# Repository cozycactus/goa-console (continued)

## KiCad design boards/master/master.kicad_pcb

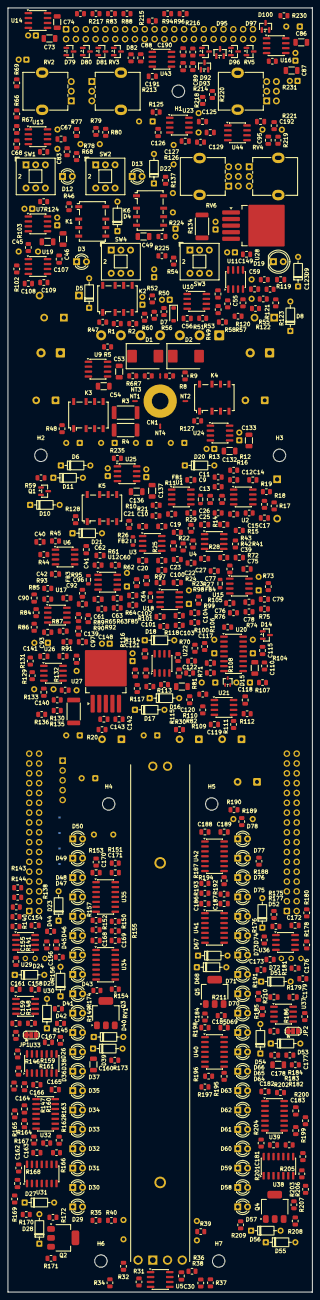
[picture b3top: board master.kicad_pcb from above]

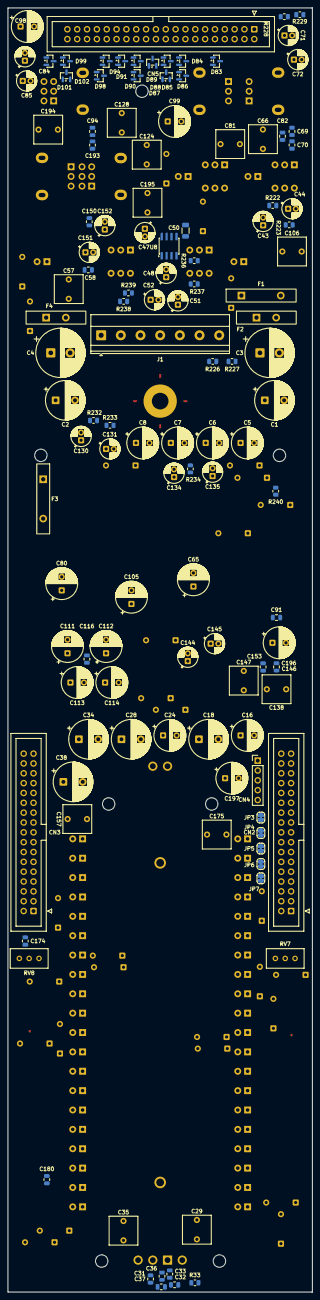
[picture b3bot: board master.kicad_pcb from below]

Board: 4 copper layers, 78.6 x 331.5 mm, 639 parts (122 on the bottom side), 387 nets, no tracks yet.

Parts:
C1, C2: 470u 25V; CP_Radial_D10.0mm_P5.00mm
C3, C4: 1000u 25V; CP_Radial_D12.5mm_P5.00mm
C5, C6, C7, C8: 47u 25V; CP_Radial_D8.0mm_P3.50mm
C9, C10, C14, C15, C19, C20, C26, C27, C30, C31, C41, C42, C55, C56, C58, C59, C60, C61, C67, C68, C75, C76, C92, C93, C100, C101, C107, C108, C115, C116, C117, C118, C119, C121, C122, C125, C126, C139, C140, C142, C143, C149, C150, C154, C155, C158, C159, C162, C163, C164, C165, C166, C167, C168, C169, C170, C171, C172, C173, C176, C177, C180, C181, C182, C183, C184, C185, C186, C187, C188, C189, C190, C191, C192, C193: 100n; C_0805_2012Metric
C11, C17, C21, C25, C33, C37, C39, C62, C69, C77, C82, C88, C89, C94, C95, C102, C146, C153: 100p C0G; C_0805_2012Metric
C12, C13, C22, C23, C63, C64, C78, C79, C103, C104: 22p C0G 5%; C_0805_2012Metric
C16, C24, C65, C80, C98, C99, C105, C111, C112, C113, C114, C196, C197: 33u NP 25V; CP_Radial_D8.0mm_P3.50mm
C18, C28, C34, C38: 100u NP 25V; CP_Radial_D10.0mm_P5.00mm
C29, C35, C66, C81, C106, C124, C128, C138, C147, C157, C175, C194, C195: 2.2u film; C_Rect_L7.2mm_W7.2mm_P5.00mm_FKS2_FKP2_MKS2_MKP2
C32, C36, C70, C83: 10p C0G; C_0805_2012Metric
C40, C109, C127, C129, C141, C148, C156, C161, C174, C179: 22p C0G; C_0805_2012Metric
C43, C44, C47, C48, C51, C52, C71, C72, C84, C85, C130, C131, C134, C135, C144, C145, C151, C152: 10u NP 25V; CP_Radial_D5.0mm_P2.00mm
C45, C46, C49, C50, C53, C54, C73, C74, C86, C87, C110, C120, C132, C133, C136, C137, C160, C178: 1u; C_1206_3216Metric
C57: 2.2u film 63V; C_Rect_L7.2mm_W7.2mm_P5.00mm_FKS2_FKP2_MKS2_MKP2
C90, C91, C96, C97: 33p C0G; C_0805_2012Metric
C123: 330n; C_0805_2012Metric
CN1: Ground bar M4 (star point); MountingHole_4.3mm_M4_Pad
CN2: Bus L wing 2x17; IDC-Header_2x17_P2.54mm_Vertical
CN3: Bus R wing 2x17; IDC-Header_2x17_P2.54mm_Vertical
CN4: Remote meter; PinHeader_1x05_P2.54mm_Vertical
CN5: Jack board link 2x20; IDC-Header_2x20_P2.54mm_Vertical
D1, D2: SS54; D_SMC
D3: Power green; LED_D3.0mm
D4, D5, D6, D8, D9, D10, D11, D16, D17, D18, D20, D21, D22, D23, D24, D25, D26, D27, D28, D39, D40, D51, D52, D53, D54, D55, D56, D67, D68: 1N4148; D_DO-35_SOD27_P7.62mm_Horizontal
D7: BZT52C6V2; D_SOD-123
D12: Aux 5 AFL red; LED_D3.0mm
D13: Aux 6 AFL red; LED_D3.0mm
D14: BZX84C5V1; SOT-23
D15: BAT54W; SOT-323_SC-70
D19: PFL ACTIVE red 5mm; LED_D5.0mm
D29, D57: green -20 dB; LED_D3.0mm
D30, D58: green -18 dB; LED_D3.0mm
D31, D59: green -16 dB; LED_D3.0mm
D32, D60: green -14 dB; LED_D3.0mm
D33, D61: green -12 dB; LED_D3.0mm
D34, D62: green -10 dB; LED_D3.0mm
D35, D63: green -8 dB; LED_D3.0mm
D36, D64: green -6 dB; LED_D3.0mm
D37, D65: green -4 dB; LED_D3.0mm
D38, D66: green -2 dB; LED_D3.0mm
D41, D69: green +0 dB; LED_D3.0mm
D42, D70: amber +2 dB; LED_D3.0mm
D43, D71: amber +4 dB; LED_D3.0mm
D44, D72: amber +6 dB; LED_D3.0mm
D45, D73: amber +8 dB; LED_D3.0mm
D46, D74: amber +10 dB; LED_D3.0mm
D47, D75: red +12 dB; LED_D3.0mm
D48, D76: red +14 dB; LED_D3.0mm
D49, D77: red +16 dB; LED_D3.0mm
D50, D78: red +18 dB; LED_D3.0mm
D79, D80, D81, D82, D83, D84, D85, D86, D87, D88, D89, D90, D91, D92, D93, D94, D95, D96, D97, D98, D99, D100, D101, D102: BAV199; SOT-23
F1, F3: MF-RX250/72; Fuse_Bourns_MF-RX250-72_Radial_P10.16mm
F2, F4: MF-RX185/72; Fuse_Bourns_MF-RX185-72_Radial_P5.08mm
FB1, FB2, FB3, FB4, FB5: Ferrite 220R@100MHz; L_0805_2012Metric
H1, H2, H3, H4, H5, H6, H7: M3 standoff 11.5 mm; MountingHole_3.2mm_M3
J1: PSU in (NC7MD-LX); TerminalBlock_Phoenix_MKDS-1,5-7-5.08_1x07_P5.08mm_Horizont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
JP1, JP2: PEAK(1-2) / AVG; SolderJumper-3_P1.3mm_Bridged12_RoundedPad1.0x1.5mm
JP3: SPARE1 to GNDA; SolderJumper-2_P1.3mm_Bridged_RoundedPad1.0x1.5mm
JP4: SPARE3 to GNDA; SolderJumper-2_P1.3mm_Bridged_RoundedPad1.0x1.5mm
JP5: SPARE5 to GNDA; SolderJumper-2_P1.3mm_Bridged_RoundedPad1.0x1.5mm
JP6: SPARE7 to GNDA; SolderJumper-2_P1.3mm_Bridged_RoundedPad1.0x1.5mm
JP7: SPARE19 to GNDA; SolderJumper-2_P1.3mm_Bridged_RoundedPad1.0x1.5mm
K1, K2, K3, K4, K5, K6: G6K-2F-Y DC12; Relay_DPDT_Omron_G6K-2F-Y
NT1: Star GNDA-GNDD; NetTie-2_SMD_Pad0.5mm
NT2: Star GNDA-GNDM; NetTie-2_SMD_Pad0.5mm
NT3: Star GNDA-PHONESGND; NetTie-2_SMD_Pad0.5mm
NT4: Star GNDA-CHASSIS; NetTie-2_SMD_Pad0.5mm
Q1: MMBT3904; SOT-23
Q2, Q3, Q4, Q5: BCP53-16; SOT-223
R1, R2: 1R; R_0805_2012Metric
R3, R4, R130, R134: 2R2; R_2512_6332Metric
R5, R6, R7, R8: 10R; R_0805_2012Metric
R9, R33, R38, R49, R56, R58, R59, R60, R67, R71, R78, R82, R104, R131, R135, R240: 4K7; R_0805_2012Metric
R10, R31, R36, R66, R70, R77, R81, R102, R109, R111, R116, R119, R120, R121, R125, R126, R129, R133: 100K; R_0805_2012Metric
R11, R21: 4K7 1%; R_0805_2012Metric
R12, R13, R14, R15, R22, R23, R24, R25, R62, R63, R64, R65, R73, R74, R75, R76, R98, R99, R100, R101: 2K2 0.1%; R_0805_2012Metric
R16, R19, R26, R29: 75R; R_0805_2012Metric
R17, R20, R27, R30, R35, R40, R51, R94, R96: 47K; R_0805_2012Metric
R18, R28: 1K; R_0805_2012Metric
R32, R37, R166, R203: 47R; R_0805_2012Metric
R34, R39, R132, R136: 2K2; R_0805_2012Metric
R41, R42, R43, R44, R45, R54, R113, R115, R118, R123, R139, R140, R142, R143, R148, R176, R177, R179, R180, R185, R239: 10K; R_0805_2012Metric
R46, R47, R48, R127, R128, R137: 560R; R_0805_2012Metric
R50: 56K; R_0805_2012Metric
R52, R69, R80: 22K; R_0805_2012Metric
R53: 64K9; R_0805_2012Metric
R55: 2M2; R_0805_2012Metric
R57: 22M; R_0805_2012Metric
R61, R72, R97: 22K 1%; R_0805_2012Metric
R68, R79: DNF (2K2 = +10 dB); R_0805_2012Metric
R83, R88, R105, R106, R107, R108, R122, R212, R217: 1M; R_0805_2012Metric
R84, R85, R86, R87, R89, R90, R91, R92: 10K 0.1%; R_0805_2012Metric
R93, R95, R103, R110, R112, R138, R175, R215, R216, R220, R221: 100R; R_0805_2012Metric
R114, R146, R183: 330K; R_0805_2012Metric
R117: 10M; R_0805_2012Metric
R124: 3K3; R_0805_2012Metric
R141, R178: 20K; R_0805_2012Metric
R144, R181: 33K; R_0805_2012Metric
R145, R159, R182, R196, R213, R214, R218, R219: 220R; R_0805_2012Metric
R147, R184: 220K; R_0805_2012Metric
R149, R156, R186, R193: 470R; R_0805_2012Metric
R150, R187: 16K; R_0805_2012Metric
R151, R188: 1K5; R_0805_2012Metric
R152, R189: 1K1; R_0805_2012Metric
R153, R190: 910R; R_0805_2012Metric
R154, R191: 680R; R_0805_2012Metric
R155, R192: 620R; R_0805_2012Metric
R157, R194: 330R; R_0805_2012Metric
R158, R195: 300R; R_0805_2012Metric
R160, R197: 180R; R_0805_2012Metric
R161, R198: 150R; R_0805_2012Metric
R162, R199: 110R; R_0805_2012Metric
R163, R170, R200, R207: 91R; R_0805_2012Metric
R164, R201: 68R; R_0805_2012Metric
R165, R202: 62R; R_0805_2012Metric
R167, R204: 33R; R_0805_2012Metric
R168, R205: 27R; R_0805_2012Metric
R169, R206: 20R; R_0805_2012Metric
R171, R173, R208, R210: 120R; R_0805_2012Metric
R172, R174, R209, R211: 27K; R_0805_2012Metric
R222, R223, R224, R225, R226, R227, R228, R229, R230, R231, R232, R233, R234, R235: 22R; R_0805_2012Metric
R236, R237: 91K; R_0805_2012Metric
R238: 51K; R_0805_2012Metric
RV1: Master fader 10K log 100mm dual; Potentiometer_Bourns_PTB0144_Slide_100mm_Dual
RV2: Aux 5 master 10K log; Potentiometer_Alpha_RD901F-40-00D_Single_Vertical
RV3: Aux 6 master 10K log; Potentiometer_Alpha_RD901F-40-00D_Single_Vertical
RV4: Solo level 10K log; Potentiometer_Alpha_RD901F-40-00D_Single_Vertical
RV5: C/Room level 10K log dual; Potentiometer_Alpha_RD902F-40-00D_Dual_Vertical
RV6: Phones level 10K log dual; Potentiometer_Alpha_RD902F-40-00D_Dual_Vertical
RV7, RV8: Cal 10K; Potentiometer_Bourns_3296W_Vertical
SW1: Aux 5 AFL; SW_Push_2P2T_Toggle_CK_PVA2xxH1xxxxxxV2
SW2: Aux 6 AFL; SW_Push_2P2T_Toggle_CK_PVA2xxH1xxxxxxV2
SW3: EXT select; SW_Push_2P2T_Toggle_CK_PVA2xxH1xxxxxxV2
SW4: C/Room DIM; SW_Push_2P2T_Toggle_CK_PVA2xxH1xxxxxxV2
U1, U2, U3, U4, U5, U6, U12, U13, U15, U17, U19, U23, U26: OPA1612; SOIC-8_3.9x4.9mm_P1.27mm
U7, U8, U9, U14, U16, U24, U25: DRV135; SOIC-8_3.9x4.9mm_P1.27mm
U10, U11, U22: LM393; SOIC-8_3.9x4.9mm_P1.27mm
U18, U21, U43, U44: OPA1656; SOIC-8_3.9x4.9mm_P1.27mm
U20: DG413; SOIC-16_3.9x9.9mm_P1.27mm
U27, U28: LME49600; TO-263-5_TabPin3
U29, U30, U36, U37: TL072; SOIC-8_3.9x4.9mm_P1.27mm
U31, U32, U33, U34, U35, U38, U39, U40, U41, U42: LM2901; SOIC-14_3.9x8.7mm_P1.27mm

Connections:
+5VL: C110.1, C115.1, D14.3, D15.1, R104.2, R116.1, U20.12
+VA: C1.1, C9.1, C14.1, C19.1, C26.1, C30.1, C41.1, C45.1, C49.1, C53.1, C60.1, C67.1, C73.1, C75.1, C86.1, C92.1, C100.1, C107.1, C116.1, C118.1, C125.1, C132.1, C136.1, C190.1, C192.1, D15.3, D79.2, D80.2, D81.2, D82.2, D83.2, D84.2, D85.2, D86.2, D87.2, D88.2, D89.2, D90.2, D91.2, D92.2, D93.2, D94.2, D95.2, D96.2, D97.2, D98.2, D99.2, D100.2, D101.2, D102.2, R1.2, R104.1, U1.8, U2.8, U3.8, U4.8, U5.8, U6.8, U7.6, U8.6, U9.6, U12.8, U13.8, U14.6, U15.8, U16.6, U17.8, U18.8, U19.8, U20.13, U21.8, U23.8, U24.6, U25.6, U43.8, U44.8
+VBUS: D1.1, F1.1, F3.1, J1.2, J1.3, R1.1, R3.1, R5.1, R7.1, R46.1, R47.1, R48.1, R49.1, R50.1, R127.1, R128.1, R137.1
+VBUS_L: CN2.32, CN2.33, CN2.34, F1.2
+VBUS_R: CN3.32, CN3.33, CN3.34, F3.2
+VL: C7.1, C55.1, C58.1, C121.1, R7.2, R9.1, R54.1, R58.1, R114.1, R119.1, R123.1, R124.1, SW1.5, SW2.5, U10.8, U11.8, U22.8
+VM: C5.1, C154.1, C158.1, C162.1, C164.1, C166.1, C168.1, C170.1, C172.1, C176.1, C180.1, C182.1, C184.1, C186.1, C188.1, CN4.3, D27.2, D39.2, D55.2, D67.2, R5.2, R150.1, R171.1, R173.1, R187.1, R208.1, R210.1, U29.8, U30.8, U31.3, U32.3, U33.3, U34.3, U35.3, U36.8, U37.8, U38.3, U39.3, U40.3, U41.3, U42.3
+VP: C3.1, C139.1, C142.1, C144.1, C149.1, C151.1, R3.2, U26.8, U27.5, U28.5
-VA: C2.2, C10.2, C15.2, C20.2, C27.2, C31.2, C42.2, C46.2, C50.2, C54.2, C61.2, C68.2, C74.2, C76.2, C87.2, C93.2, C101.2, C108.2, C117.2, C119.2, C126.2, C133.2, C137.2, C191.2, C193.2, D79.1, D80.1, D81.1, D82.1, D83.1, D84.1, D85.1, D86.1, D87.1, D88.1, D89.1, D90.1, D91.1, D92.1, D93.1, D94.1, D95.1, D96.1, D97.1, D98.1, D99.1, D100.1, D101.1, D102.1, R2.2, U1.4, U2.4, U3.4, U4.4, U5.4, U6.4, U7.5, U8.5, U9.5, U12.4, U13.4, U14.5, U15.4, U16.5, U17.4, U18.4, U19.4, U20.4, U21.4, U23.4, U24.5, U25.5, U43.4, U44.4
-VBUS: D2.2, F2.1, F4.1, J1.6, J1.7, R2.1, R4.1, R6.1, R8.1, R53.2
-VBUS_L: CN2.30, CN2.31, F2.2
-VBUS_R: CN3.30, CN3.31, F4.2
-VL: C8.2, C56.2, C59.2, C122.2, R8.2, U10.4, U11.4, U22.4
-VM: C6.2, C155.2, C159.2, C163.2, C165.2, C167.2, C169.2, C171.2, C173.2, C177.2, C181.2, C183.2, C185.2, C187.2, C189.2, CN4.5, D38.1, D50.1, D66.1, D78.1, R6.2, R172.2, R174.2, R209.2, R211.2, U29.4, U30.4, U31.12, U32.12, U33.12, U34.12, U35.12, U36.4, U37.4, U38.12, U39.12, U40.12, U41.12, U42.12
-VP: C4.2, C140.2, C143.2, C145.2, C150.2, C152.2, R4.2, U26.4, U27.3, U28.3
A5_AFLC: C194.2, R69.1
A5_AFLJ: R69.2, SW1.2
A5_MIX: C63.1, C65.1, R63.2, U12.7
A5_ON: C72.2, CN5.20, D90.3, U14.2
A5_OP: C71.2, CN5.19, D89.3, U14.7
A5_OUT: C69.1, C194.1, R67.1, U13.1, U14.4
A5_PT: C65.2, RV2.3
A5_SUM: C62.1, R61.1, R62.1, U12.1
A5_W: C66.1, RV2.2
A6_AFLC: C195.2, R80.1
A6_AFLJ: R80.2, SW2.2
A6_MIX: C78.1, C80.1, R74.2, U15.7
A6_ON: C85.2, CN5.23, D92.3, U16.2
A6_OP: C84.2, CN5.22, D91.3, U16.7
A6_OUT: C82.1, C195.1, R78.1, U13.7, U16.4
A6_PT: C80.2, RV3.3
A6_SUM: C77.1, R72.1, R73.1, U15.1
A6_W: C81.1, RV3.2
AUX1: CN2.24, CN3.24
AUX2: CN2.25, CN3.25
AUX3: CN2.23, CN3.23
AUX4: CN2.22, CN3.22
AUX5: CN2.21, CN3.21, FB3.1
AUX6: CN2.20, CN3.20, FB4.1
CHASSIS: CN5.9, J1.1, NT4.2
CRL_N: C131.2, K4.5, U24.2
CRL_P: C130.2, K4.4, U24.7
CRL_XN: CN5.32, D98.3, K4.6
CRL_XP: CN5.31, D97.3, K4.3
CRO_L: U23.1, U23.2, U24.4
CRO_R: U23.6, U23.7, U25.4
CRP_L: R236.2, RV5.3, SW4.3
CRP_R: R237.2, RV5.6, SW4.6
CRR_N: C135.2, K5.5, U25.2
CRR_P: C134.2, K5.4, U25.7
CRR_XN: CN5.35, D100.3, K5.6
CRR_XP: CN5.34, D99.3, K5.3
CRSB_L: R110.2, R138.1, R236.1, RV6.3, SW4.2
CRSB_LO: R110.1, U21.1, U21.2
CRSB_R: R112.2, R175.1, R237.1, RV6.6, SW4.5
CRSB_RO: R112.1, U21.6, U21.7
CRS_L: R109.1, U20.2, U20.15, U21.3
CRS_R: R111.1, U20.7, U20.10, U21.5
CRW_L: C124.1, RV5.2
CRW_R: C128.1, RV5.5
EXT_BL: C90.2, R85.2, R93.1, U17.1
EXT_BL_RB: R84.1, R216.2
EXT_BL_TB: R86.1, R215.2
EXT_BR: C96.2, R90.2, R95.1, U17.7
EXT_BR_RB: R89.1, R221.2
EXT_BR_TB: R91.1, R220.2
EXT_L: C98.2, R94.1, SW3.1
EXT_LR: CN5.26, D94.3, R212.1, R214.1
EXT_LT: CN5.25, D93.3, R83.1, R213.1
EXT_R: C99.2, R96.1, SW3.4
EXT_RR: CN5.29, D96.3, R217.1, R219.1
EXT_RT: CN5.28, D95.3, R88.1, R218.1
FL_HOLD: D18.1, U22.7
FL_N: C123.1, D18.2, R122.2, U11.6
FL_OUT: D19.1, R121.1, R122.1, R123.2, U11.7
FL_P: R119.2, R120.1, R121.2, U11.5
GCANCEL: CN2.26, CN3.26, R10.1, U1.3, U1.5, U3.3, U12.3, U15.3, U18.3
GCANCEL_BUF: R14.1, R24.1, R64.1, R75.1, R100.1, U1.1, U1.2
GNDA: C1.2, C2.1, C3.2, C4.1, C9.2, C10.1, C13.2, C14.2, C15.1, C17.2, C19.2, C20.1, C23.2, C25.2, C26.2, C27.1, C30.2, C31.1, C32.2, C36.2, C41.2, C42.1, C45.2, C46.1, C49.2, C50.1, C53.2, C54.1, C60.2, C61.1, C64.2, C67.2, C68.1, C70.2, C73.2, C74.1, C75.2, C76.1, C79.2, C83.2, C86.2, C87.1, C88.2, C89.2, C91.2, C92.2, C93.1, C94.2, C95.2, C97.2, C100.2, C101.1, C104.2, C107.2, C108.1, C109.2, C116.2, C117.1, C118.2, C119.1, C125.2, C126.1, C127.2, C129.2, C132.2, C133.1, C136.2, C137.1, C139.2, C140.1, C141.2, C142.2, C143.1, C144.2, C145.1, C148.2, C149.2, C150.1, C151.2, C152.1, C190.2, C191.1, C192.2, C193.1, C196.2, C197.2, CN1.1, CN2.2, CN2.4, CN2.6, CN2.8, CN2.10, CN2.12, CN2.14, CN2.16, CN3.2, CN3.4, CN3.6, CN3.8, CN3.10, CN3.12, CN3.14, CN3.16, CN5.2, CN5.4, CN5.6, CN5.8, CN5.12, CN5.15, CN5.18, CN5.21, CN5.24, CN5.27, CN5.30, CN5.33, CN5.36, CN5.40, D1.2, D2.1, J1.4, J1.5, JP3.2, JP4.2, JP5.2, JP6.2, JP7.2, K1.2, K1.7, K2.2, K2.7, K3.2, K3.7, K4.2, K4.7, K5.2, K5.7, NT1.1, NT2.1, NT3.1, NT4.1, R10.2, R15.2, R17.2, R20.2, R25.2, R27.2, R30.2, R31.2, R34.2, R35.2, R36.2, R39.2, R40.2, R65.2, R66.2, R68.2, R76.2, R77.2, R79.2, R83.2, R87.2, R88.2, R92.2, R94.2, R96.2, R101.2, R102.2, R105.2, R106.2, R107.2, R108.2, R109.2, R111.2, R125.2, R126.2, R129.2, R133.2, R212.2, R217.2, RV1.1, RV1.4, RV2.1, RV3.1, RV4.1, RV5.1, RV5.4, RV6.1, RV6.4, SW1.3, SW2.3, U4.5, U6.3, U6.5, U7.3, U8.3, U9.3, U14.3, U16.3, U19.5, U24.3, U25.3
GNDD: C7.2, C8.1, C55.2, C56.1, C57.2, C58.2, C59.1, C110.2, C115.2, C120.2, C121.2, C122.1, C123.2, D3.1, D7.2, D9.2, D11.2, D12.1, D13.1, D14.1, D17.1, NT1.2, Q1.2, R51.2, R113.2, R115.2, R120.2, R239.2, R240.2, U20.5
GNDM: C5.2, C6.1, C154.2, C155.1, C157.2, C158.2, C159.1, C160.2, C162.2, C163.1, C164.2, C165.1, C166.2, C167.1, C168.2, C169.1, C170.2, C171.1, C172.2, C173.1, C175.2, C176.2, C177.1, C178.2, C180.2, C181.1, C182.2, C183.1, C184.2, C185.1, C186.2, C187.1, C188.2, C189.1, CN4.4, NT2.2, R147.2, R170.2, R184.2, R207.2, U29.3, U29.5, U36.3, U36.5
MAIN_L_N: C44.2, K1.5, U7.2
MAIN_L_P: C43.2, K1.4, U7.7
MAIN_L_XN: CN5.11, D84.3, K1.6
MAIN_L_XP: CN5.10, D83.3, K1.3
MAIN_M_N: C52.2, K3.5, U9.2
MAIN_M_P: C51.2, K3.4, U9.7
MAIN_M_XN: CN5.17, D88.3, K3.6
MAIN_M_XP: CN5.16, D87.3, K3.3
MAIN_R_N: C48.2, K2.5, U8.2
MAIN_R_P: C47.2, K2.4, U8.7
MAIN_R_XN: CN5.14, D86.3, K2.6
MAIN_R_XP: CN5.13, D85.3, K2.3
MIXL: CN2.18, CN3.18, FB1.1
MIXR: CN2.17, CN3.17, FB2.1
MIX_L: C12.1, R13.2, R16.1, U2.1
MIX_L_RETRAW: C16.1, CN5.3, D80.3
MIX_L_SEND: CN5.1, D79.3, R16.2
MIX_R: C22.1, R23.2, R26.1, U3.7
MIX_R_RETRAW: C24.1, CN5.7, D82.3
MIX_R_SEND: CN5.5, D81.3, R26.2
MLA_5: D33.1, D34.2, U32.1
MLA_QB: D28.1, Q2.1, R172.1
MLA_QE: Q2.3, R171.2
MLB_5: D45.1, D46.2, U34.14
MLB_QB: D40.1, Q3.1, R174.1
MLB_QE: Q3.3, R173.2
ML_DET: R149.2, U31.5, U31.7, U31.9, U31.11, U32.5, U32.7, U32.9, U32.11, U33.5, U33.7, U33.9, U33.11, U34.5, U34.7, U34.9, U34.11, U35.5, U35.7, U35.9, U35.11
ML_DETO: R148.1, R149.1, U30.6, U30.7
ML_HW: D23.2, R140.2, R142.1
ML_T1: R169.2, R170.1, U31.4
ML_T2: R168.2, R169.1, U31.6
ML_T3: R167.2, R168.1, U31.10
ML_T4: R166.2, R167.1, U31.8
ML_T5: R165.2, R166.1, U32.4
ML_T6: R164.2, R165.1, U32.6
ML_T7: R163.2, R164.1, U32.10
ML_T8: R162.2, R163.1, U32.8
ML_T9: R161.2, R162.1, U33.4
ML_T10: R160.2, R161.1, U33.6
ML_T11: R159.2, R160.1, U33.10
ML_T12: R158.2, R159.1, U33.8
ML_T13: R157.2, R158.1, U34.4
ML_T14: R156.2, R157.1, U34.6
ML_T15: R155.2, R156.1, U34.10
ML_T16: R154.2, R155.1, U34.8
ML_T17: R153.2, R154.1, U35.4
ML_T18: R152.2, R153.1, U35.6
ML_T19: R151.2, R152.1, U35.10
ML_T20: R150.2, R151.1, U35.8
ML_X2: C156.1, R143.1, R144.1, U29.7, U30.3
MONO: C40.1, R45.2, U6.1, U9.4
MONO_INV: C39.1, R43.1, R44.1, U4.7
MON_L: C111.1, SW3.2
MON_R: C113.1, SW3.5
MRA_5: D61.1, D62.2, U39.1
MRA_QB: D56.1, Q4.1, R209.1
MRA_QE: Q4.3, R208.2
MRB_5: D73.1, D74.2, U41.14
MRB_QB: D68.1, Q5.1, R211.1
MRB_QE: Q5.3, R210.2
MR_DET: R186.2, U38.5, U38.7, U38.9, U38.11, U39.5, U39.7, U39.9, U39.11, U40.5, U40.7, U40.9, U40.11, U41.5, U41.7, U41.9, U41.11, U42.5, U42.7, U42.9, U42.11
MR_DETO: R185.1, R186.1, U37.6, U37.7
MR_HW: D51.2, R177.2, R179.1
MR_T1: R206.2, R207.1, U38.4
MR_T2: R205.2, R206.1, U38.6
MR_T3: R204.2, R205.1, U38.10
MR_T4: R203.2, R204.1, U38.8
MR_T5: R202.2, R203.1, U39.4
MR_T6: R201.2, R202.1, U39.6
MR_T7: R200.2, R201.1, U39.10
MR_T8: R199.2, R200.1, U39.8
MR_T9: R198.2, R199.1, U40.4
MR_T10: R197.2, R198.1, U40.6
MR_T11: R196.2, R197.1, U40.10
MR_T12: R195.2, R196.1, U40.8
MR_T13: R194.2, R195.1, U41.4
MR_T14: R193.2, R194.1, U41.6
MR_T15: R192.2, R193.1, U41.10
MR_T16: R191.2, R192.1, U41.8
MR_T17: R190.2, R191.1, U42.4
MR_T18: R189.2, R190.1, U42.6
MR_T19: R188.2, R189.1, U42.10
MR_T20: R187.2, R188.1, U42.8
MR_X2: C174.1, R180.1, R181.1, U36.7, U37.3
MTR_L: CN4.1, R138.2, R139.1, R141.1
MTR_R: CN4.2, R175.2, R176.1, R178.1
MUTE_GO: R57.1, R58.2, R59.1, U11.1
MUTE_T: C57.1, D8.2, D9.1, R55.2, R57.2, U11.3
MW_L: C29.1, RV1.2
MW_R: C35.1, RV1.5
unnamed: C16.2, R17.1, R18.1
unnamed: C18.1, R19.2
unnamed: C24.2, R27.1, R28.1
unnamed: C28.1, R29.2
unnamed: C33.1, R32.1, R33.1, U5.1
unnamed: C34.1, R32.2
unnamed: C37.1, R37.1, R38.1, U5.7
unnamed: C38.1, R37.2
unnamed: C43.1, R222.2
unnamed: C44.1, R223.2
unnamed: C47.1, R224.2
unnamed: C48.1, R225.2
unnamed: C51.1, R226.2
unnamed: C52.1, R227.2
unnamed: C71.1, R228.2
unnamed: C72.1, R229.2
unnamed: C84.1, R230.2
unnamed: C85.1, R231.2
unnamed: C98.1, R93.2
unnamed: C99.1, R95.2
unnamed: C130.1, R232.2
unnamed: C131.1, R233.2
unnamed: C134.1, R234.2
unnamed: C135.1, R235.2
unnamed: C160.1, R145.2, R146.1
unnamed: C178.1, R182.2, R183.1
unnamed: D3.2, R9.2
unnamed: D4.1, K1.1, R46.2
unnamed: D5.1, K2.1, R47.2
unnamed: D6.1, K3.1, R48.2
unnamed: D8.1, R56.1
unnamed: D10.1, R60.1
unnamed: D12.2, R71.2
unnamed: D13.2, R82.2
unnamed: D16.1, D17.2
unnamed: D19.2, R124.2
unnamed: D20.1, K4.1, R127.2
unnamed: D21.1, K5.1, R128.2
unnamed: D22.1, K6.1, R137.2
unnamed: D23.1, D24.2, U29.1
unnamed: D24.1, R139.2, R140.1, U29.2
unnamed: C161.1, D25.2, D26.1, U30.1
unnamed: D25.1, JP1.1, R145.1
unnamed: C161.2, D26.2, R148.2, U30.2
unnamed: D27.1, D28.2
unnamed: D29.2, Q2.2, Q2.4, U31.2
unnamed: D29.1, D30.2, U31.1
unnamed: D30.1, D31.2, U31.13
unnamed: D31.1, D32.2, U31.14
unnamed: D32.1, D33.2, U32.2
unnamed: D34.1, D35.2, U32.13
unnamed: D35.1, D36.2, U32.14
unnamed: D36.1, D37.2, U33.2
unnamed: D37.1, D38.2, U33.1
unnamed: D39.1, D40.2
unnamed: D41.2, Q3.2, Q3.4, U33.13
unnamed: D41.1, D42.2, U33.14
unnamed: D42.1, D43.2, U34.2
unnamed: D43.1, D44.2, U34.1
unnamed: D44.1, D45.2, U34.13
unnamed: D46.1, D47.2, U35.2
unnamed: D47.1, D48.2, U35.1
unnamed: D48.1, D49.2, U35.13
unnamed: D49.1, D50.2, U35.14
unnamed: D51.1, D52.2, U36.1
unnamed: D52.1, R176.2, R177.1, U36.2
unnamed: C179.1, D53.2, D54.1, U37.1
unnamed: D53.1, JP2.1, R182.1
unnamed: C179.2, D54.2, R185.2, U37.2
unnamed: D55.1, D56.2
unnamed: D57.2, Q4.2, Q4.4, U38.2
unnamed: D57.1, D58.2, U38.1
unnamed: D58.1, D59.2, U38.13
unnamed: D59.1, D60.2, U38.14
unnamed: D60.1, D61.2, U39.2
unnamed: D62.1, D63.2, U39.13
unnamed: D63.1, D64.2, U39.14
unnamed: D64.1, D65.2, U40.2
unnamed: D65.1, D66.2, U40.1
unnamed: D67.1, D68.2
unnamed: D69.2, Q5.2, Q5.4, U40.13
unnamed: D69.1, D70.2, U40.14
unnamed: D70.1, D71.2, U41.2
unnamed: D71.1, D72.2, U41.1
unnamed: D72.1, D73.2, U41.13
unnamed: D74.1, D75.2, U42.2
unnamed: D75.1, D76.2, U42.1
unnamed: D76.1, D77.2, U42.13
unnamed: D77.1, D78.2, U42.14
unnamed: C157.1, JP1.3, R144.2
unnamed: JP1.2, U30.5
unnamed: C175.1, JP2.3, R181.2
unnamed: JP2.2, U37.5
unnamed: R130.1, U27.4
unnamed: R134.1, U28.4
unnamed: R143.2, RV7.1
unnamed: R146.2, R147.1
unnamed: R180.2, RV8.1
unnamed: R183.2, R184.1
unnamed: R70.1, R71.1, SW1.4
unnamed: R81.1, R82.1, SW2.4
unnamed: C11.2, FB1.2, R11.2, U1.6
unnamed: C13.1, R14.2, R15.1, U2.3
unnamed: C12.2, R12.2, R13.1, U2.2
unnamed: C17.1, R18.2, U2.5
unnamed: R19.1, U2.6, U2.7
unnamed: C21.2, FB2.2, R21.2, U3.2
unnamed: C23.1, R24.2, R25.1, U3.5
unnamed: C22.2, R22.2, R23.1, U3.6
unnamed: C25.1, R28.2, U4.3
unnamed: R29.1, U4.1, U4.2
unnamed: C39.2, R41.2, R42.2, R43.2, U4.6
unnamed: C29.2, C32.1, R31.1, U5.3
unnamed: C33.2, R33.2, R34.1, U5.2
unnamed: C35.2, C36.1, R36.1, U5.5
unnamed: C37.2, R38.2, R39.1, U5.6
unnamed: C40.2, R44.2, R45.1, U6.2
unnamed: U6.6, U6.7
unnamed: R222.1, U7.8
unnamed: R223.1, U7.1
unnamed: R224.1, U8.8
unnamed: R225.1, U8.1
unnamed: R226.1, U9.8
unnamed: R227.1, U9.1
unnamed: C62.2, FB3.2, R61.2, U12.2
unnamed: C64.1, R64.2, R65.1, U12.5
unnamed: C63.2, R62.2, R63.1, U12.6
unnamed: C66.2, C70.1, R66.1, U13.3
unnamed: C69.2, R67.2, R68.1, U13.2
unnamed: C81.2, C83.1, R77.1, U13.5
unnamed: C82.2, R78.2, R79.1, U13.6
unnamed: R228.1, U14.8
unnamed: R229.1, U14.1
unnamed: C77.2, FB4.2, R72.2, U15.2
unnamed: C79.1, R75.2, R76.1, U15.5
unnamed: C78.2, R73.2, R74.1, U15.6
unnamed: R230.1, U16.8
unnamed: R231.1, U16.1
unnamed: C91.1, R86.2, R87.1, U17.3
unnamed: C90.1, R84.2, R85.1, U17.2
unnamed: C97.1, R91.2, R92.1, U17.5
unnamed: C96.1, R89.2, R90.1, U17.6
unnamed: C102.2, FB5.2, R97.2, U18.2
unnamed: C104.1, R100.2, R101.1, U18.5
unnamed: C103.2, R98.2, R99.1, U18.6
unnamed: C106.2, C109.1, R102.1, U19.3
unnamed: R103.1, U19.1, U19.2
unnamed: U19.6, U19.7
unnamed: C124.2, C127.1, R125.1, U23.3
unnamed: C128.2, C129.1, R126.1, U23.5
unnamed: R232.1, U24.8
unnamed: R233.1, U24.1
unnamed: R234.1, U25.8
unnamed: R235.1, U25.1
unnamed: C138.2, C141.1, R129.1, U26.3
unnamed: C146.2, R131.2, R132.1, U26.2
unnamed: C147.2, C148.1, R133.1, U26.5
unnamed: C153.2, R135.2, R136.1, U26.6
unnamed: C146.1, U26.1, U27.2
unnamed: C153.1, U26.7, U28.2
unnamed: C156.2, R141.2, R142.2, RV7.2, RV7.3, U29.6
unnamed: C174.2, R178.2, R179.2, RV8.2, RV8.3, U36.6
unnamed: C88.1, R213.2, U43.3
unnamed: R215.1, U43.1, U43.2
unnamed: C89.1, R214.2, U43.5
unnamed: R216.1, U43.6, U43.7
unnamed: C94.1, R218.2, U44.3
unnamed: R220.1, U44.1, U44.2
unnamed: C95.1, R219.2, U44.5
unnamed: R221.1, U44.6, U44.7
PFL: CN2.27, CN3.27, FB5.1, SW1.1, SW2.1
PFLDET: C120.1, CN2.29, CN3.29, D16.2, R70.2, R81.2, R113.1, R117.2, U22.3, U22.5
PFLN: CN2.28, CN3.28
PFL_MIX: C103.1, C105.1, R99.2, U18.7
PFL_ON: R118.2, U20.1, U20.8, U20.9, U20.16
PFL_ON_RAW: R116.2, R117.1, R118.1, U22.1
PFL_PT: C105.2, RV4.3
PFL_REF: R114.2, R115.1, U22.2, U22.6
PFL_SIG: C112.1, C114.1, R103.2
PFL_SUM: C102.1, R97.1, R98.1, U18.1
PFL_W: C106.1, RV4.2
PHJ_L: CN5.37, D101.3, K6.3
PHJ_R: CN5.38, D102.3, K6.6
PHONESGND: CN5.39, K6.2, K6.7, NT3.2
PHO_L: K6.4, R130.2, R131.1
PHO_R: K6.5, R134.2, R135.1
PHW_L: C138.1, RV6.2
PHW_R: C147.1, RV6.5
PH_GL: C196.1, R132.2
PH_GR: C197.1, R136.2
POST_L: C34.2, R35.1, R41.1, SW3.3, U7.4
POST_R: C38.2, R40.1, R42.1, SW3.6, U8.4
PRE_L: C18.2, R20.1, RV1.3
PRE_R: C28.2, R30.1, RV1.6
RAIL_OK: R54.2, R55.1, R56.2, R60.2, U10.1, U10.7
RLY_B: D10.2, D11.1, Q1.1, R59.2, R240.1
RLY_DRV: D4.2, D5.2, D6.2, D20.2, D21.2, D22.2, K1.8, K2.8, K3.8, K4.8, K5.8, K6.8, Q1.3
SENSE_N: R52.2, R53.1, U10.6
SENSE_P: R50.2, R51.1, U10.3
SENSE_REF: R238.2, R239.1, U10.5
SPARE1: CN2.1, CN3.1, JP3.1
SPARE3: CN2.3, CN3.3, JP4.1
SPARE5: CN2.5, CN3.5, JP5.1
SPARE7: CN2.7, CN3.7, JP6.1
SPARE19: CN2.19, CN3.19, JP7.1
SUB1: CN2.15, CN3.15
SUB2: CN2.13, CN3.13
SUB3: CN2.11, CN3.11
SUB4: CN2.9, CN3.9
SUM_L: C11.1, R11.1, R12.1, U1.7
SUM_R: C21.1, R21.1, R22.1, U3.1
SWML_S: C111.2, R105.1, U20.14
SWMR_S: C113.2, R107.1, U20.11
SWPL_S: C112.2, R106.1, U20.3
SWPR_S: C114.2, R108.1, U20.6
VREF6: D7.1, R49.2, R52.1, R238.1, U10.2, U11.2

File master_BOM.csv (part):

"Qty","Value","Footprint","MPN","DNP","References"
"2","470u 25V","Capacitor_THT:CP_Radial_D10.0mm_P5.00mm","Nichicon UPW1E471MPD","","C1 C2"
"2","1000u 25V","Capacitor_THT:CP_Radial_D12.5mm_P5.00mm","Nichicon UPW1E102MHD","","C3 C4"
"4","47u 25V","Capacitor_THT:CP_Radial_D8.0mm_P3.50mm","Nichicon UPW1J470MPD (63V)","","C5 C6 C7 C8"
"75","100n","Capacitor_SMD:C_0805_2012Metric","Samsung CL21B104KBCNNNC (X7R 50V)","","C9 C10 C14 C15 C19 C20 C26 C27 C30 C31 C41 C42 C55 C56 C58 C59 C60 C61 C67 C68 C75 C76 C92 C93 C100 C101 C107 C108 C115 C116 C117 C118 C119 C121 C122 C125 C126 C139 C140 C142 C143 C149 C150 C154 C155 C158 C159 C162 C163 C164 C165 C166 C167 C168 C169 C170 C171 C172 C173 C176 C177 C180 C181 C182 C183 C184 C185 C186 C187 C188 C189 C190 C191 C192 C193"
"18","100p C0G","Capacitor_SMD:C_0805_2012Metric","KEMET C0805C101J5GACTU","","C11 C17 C21 C25 C33 C37 C39 C62 C69 C77 C82 C88 C89 C94 C95 C102 C146 C153"
"10","22p C0G 5%","Capacitor_SMD:C_0805_2012Metric","KEMET C0805C220J5GACTU","","C12 C13 C22 C23 C63 C64 C78 C79 C103 C104"
"11","33u NP 25V","Capacitor_THT:CP_Radial_D8.0mm_P3.50mm","Nichicon UES1E330MPM (MUSE ES)","","C16 C24 C65 C80 C98 C99 C105 C111 C112 C113 C114"
"4","100u NP 25V","Capacitor_THT:CP_Radial_D10.0mm_P5.00mm","Nichicon UES1E101MPM (MUSE ES)","","C18 C28 C34 C38"
"11","2.2u film","Capacitor_THT:C_Rect_L7.2mm_W7.2mm_P5.00mm_FKS2_FKP2_MKS2_MKP2","WIMA MKS2C042201K00KSSD (PET 63V)","","C29 C35 C66 C81 C106 C124 C128 C138 C147 C157 C175"
"4","10p C0G","Capacitor_SMD:C_0805_2012Metric","KEMET C0805C100J5GACTU","","C32 C36 C70 C83"
"10","22p C0G","Capacitor_SMD:C_0805_2012Metric","KEMET C0805C220J5GACTU","","C40 C109 C127 C129 C141 C148 C156 C161 C174 C179"
"18","10u NP 25V","Capacitor_THT:CP_Radial_D5.0mm_P2.00mm","Panasonic ECE-A1EN100U","","C43 C44 C47 C48 C51 C52 C71 C72 C84 C85 C130 C131 C134 C135 C144 C145 C151 C152"
"18","1u","Capacitor_SMD:C_1206_3216Metric","Samsung CL31B105KBHNNNE (X7R 50V)","","C45 C46 C49 C50 C53 C54 C73 C74 C86 C87 C110 C120 C132 C133 C136 C137 C160 C178"
"1","2.2u film 63V","Capacitor_THT:C_Rect_L7.2mm_W7.2mm_P5.00mm_FKS2_FKP2_MKS2_MKP2","WIMA MKS2C042201K00KSSD (PET 63V)","","C57"
"4","33p C0G","Capacitor_SMD:C_0805_2012Metric","KEMET C0805C330J5GACTU","","C90 C91 C96 C97"
"1","330n","Capacitor_SMD:C_0805_2012Metric","Samsung CL21B334KBFNNNE (X7R 50V)","","C123"
"1","Ground bar M4 (star point)","MountingHole:MountingHole_4.3mm_M4_Pad","","","CN1"
"1","Bus L wing 2x17","Connector_IDC:IDC-Header_2x17_P2.54mm_Vertical","Wurth 61203421621 (2x17 box header)","","CN2"
"1","Bus R wing 2x17","Connector_IDC:IDC-Header_2x17_P2.54mm_Vertical","Wurth 61203421621 (2x17 box header)","","CN3"
"1","Remote meter","Connector_PinHeader_2.54mm:PinHeader_1x05_P2.54mm_Vertical","Sullins PRPC005SAAN-RC","","CN4"
"1","Jack board link 2x20","Connector_IDC:IDC-Header_2x20_P2.54mm_Vertical","Wurth 61204021621 (2x20 box header)","","CN5"
"2","SS54","Diode_SMD:D_SMC","Diodes B540C-13-F (SS54 class, SMC 40 V 5 A)","","D1 D2"
"1","Power green","LED_THT:LED_D3.0mm","Kingbright WP710A10GD","","D3"
"29","1N4148","Diode_THT:D_DO-35_SOD27_P7.62mm_Horizontal","Vishay 1N4148-TAP","","D4 D5 D6 D8 D9 D10 D11 D16 D17 D18 D20 D21 D22 D23 D24 D25 D26 D27 D28 D39 D40 D51 D52 D53 D54 D55 D56 D67 D68"
"1","BZT52C6V2","Diode_SMD:D_SOD-123","Diodes BZT52C6V2-7-F","","D7"
"1","Aux 5 AFL red","LED_THT:LED_D3.0mm","Kingbright WP710A10ID","","D12"
"1","Aux 6 AFL red","LED_THT:LED_D3.0mm","Kingbright WP710A10ID","","D13"
"1","BZX84C5V1","Package_TO_SOT_SMD:SOT-23","Nexperia BZX84-C5V1,215","","D14"
"1","BAT54W","Package_TO_SOT_SMD:SOT-323_SC-70","Nexperia BAT54W,115","","D15"
"1","PFL ACTIVE red 5mm","LED_THT:LED_D5.0mm","Kingbright WP7113ID","","D19"
"2","green -20 dB","LED_THT:LED_D3.0mm","Kingbright WP710A10GD","","D29 D57"
"2","green -18 dB","LED_THT:LED_D3.0mm","Kingbright WP710A10GD","","D30 D58"
"2","green -16 dB","LED_THT:LED_D3.0mm","Kingbright WP710A10GD","","D31 D59"
"2","green -14 dB","LED_THT:LED_D3.0mm","Kingbright WP710A10GD","","D32 D60"
"2","green -12 dB","LED_THT:LED_D3.0mm","Kingbright WP710A10GD","","D33 D61"
"2","green -10 dB","LED_THT:LED_D3.0mm","Kingbright WP710A10GD","","D34 D62"
"2","green -8 dB","LED_THT:LED_D3.0mm","Kingbright WP710A10GD","","D35 D63"
"2","green -6 dB","LED_THT:LED_D3.0mm","Kingbright WP710A10GD","","D36 D64"
"2","green -4 dB","LED_THT:LED_D3.0mm","Kingbright WP710A10GD","","D37 D65"
"2","green -2 dB","LED_THT:LED_D3.0mm","Kingbright WP710A10GD","","D38 D66"
"2","green +0 dB","LED_THT:LED_D3.0mm","Kingbright WP710A10GD","","D41 D69"
"2","amber +2 dB","LED_THT:LED_D3.0mm","Kingbright WP710A10ND","","D42 D70"
"2","amber +4 dB","LED_THT:LED_D3.0mm","Kingbright WP710A10ND","","D43 D71"
"2","amber +6 dB","LED_THT:LED_D3.0mm","Kingbright WP710A10ND","","D44 D72"
"2","amber +8 dB","LED_THT:LED_D3.0mm","Kingbright WP710A10ND","","D45 D73"
"2","amber +10 dB","LED_THT:LED_D3.0mm","Kingbright WP710A10ND","","D46 D74"
"2","red +12 dB","LED_THT:LED_D3.0mm","Kingbright WP710A10ID","","D47 D75"
"2","red +14 dB","LED_THT:LED_D3.0mm","Kingbright WP710A10ID","","D48 D76"
"2","red +16 dB","LED_THT:LED_D3.0mm","Kingbright WP710A10ID","","D49 D77"
"2","red +18 dB","LED_THT:LED_D3.0mm","Kingbright WP710A10ID","","D50 D78"
"2","MF-RX250/72","goa-console:Fuse_Bourns_MF-RX250-72_Radial_P10.16mm","Bourns MF-RX250/72-0","","F1 F3"
"2","MF-RX185/72","goa-console:Fuse_Bourns_MF-RX185-72_Radial_P5.08mm","Bourns MF-RX185/72-0","","F2 F4"
"5","Ferrite 220R@100MHz","Inductor_SMD:L_0805_2012Metric","Murata BLM21PG221SN1D","","FB1 FB2 FB3 FB4 FB5"
"1","PSU in (NC7MD-LX)","TerminalBlock_Phoenix:TerminalBlock_Phoenix_MKDS-1,5-7-5.08_1x07_P5.08mm_Horizontal","Phoenix 1755897 MKDS 1,5/7-5,08 (wired to a Neutrik NC7MD-LX inlet)","","J1"
"6","G6K-2F-Y DC12","Relay_SMD:Relay_DPDT_Omron_G6K-2F-Y","Omron G6K-2F-Y DC12","","K1 K2 K3 K4 K5 K6"
"1","MMBT3904","Package_TO_SOT_SMD:SOT-23","onsemi MMBT3904LT1G","","Q1"
"4","BCP53-16","Package_TO_SOT_SMD:SOT-223","onsemi BCP53-16T1G","","Q2 Q3 Q4 Q5"
"2","1R","Resistor_SMD:R_0805_2012Metric","Panasonic ERJ-P06J1R0V","","R1 R2"
"4","2R2","Resistor_SMD:R_2512_6332Metric","Vishay CRCW25122R20FKEGHP","","R3 R4 R130 R134"
"4","10R","Resistor_SMD:R_0805_2012Metric","","","R5 R6 R7 R8"
"14","4K7","Resistor_SMD:R_0805_2012Metric","","","R9 R33 R38 R49 R56 R59 R60 R67 R71 R78 R82 R104 R131 R135"
"18","100K","Resistor_SMD:R_0805_2012Metric","","","R10 R31 R36 R66 R70 R77 R81 R102 R109 R111 R116 R119 R120 R121 R125 R126 R129 R133"
"2","4K7 1%","Resistor_SMD:R_0805_2012Metric","","","R11 R21"
"20","2K2 0.1%","Resistor_SMD:R_0805_2012Metric","Panasonic ERA-6AEB222V","","R12 R13 R14 R15 R22 R23 R24 R25 R62 R63 R64 R65 R73 R74 R75 R76 R98 R99 R100 R101"
"2","75R","Resistor_SMD:R_0805_2012Metric","Panasonic ERJ-P06J750V","","R16 R26"
"9","47K","Resistor_SMD:R_0805_2012Metric","","","R17 R20 R27 R30 R35 R40 R51 R94 R96"
"2","1K","Resistor_SMD:R_0805_2012Metric","","","R18 R28"
"2","75R","Resistor_SMD:R_0805_2012Metric","","","R19 R29"
"4","47R","Resistor_SMD:R_0805_2012Metric","","","R32 R37 R166 R203"
"4","2K2","Resistor_SMD:R_0805_2012Metric","","","R34 R39 R132 R136"
"19","10K","Resistor_SMD:R_0805_2012Metric","","","R41 R42 R43 R44 R45 R113 R115 R118 R123 R139 R140 R142 R143 R148 R176 R177 R179 R180 R185"
"6","560R","Resistor_SMD:R_0805_2012Metric","","","R46 R47 R48 R127 R128 R137"
"1","56K","Resistor_SMD:R_0805_2012Metric","","","R50"
"3","22K","Resistor_SMD:R_0805_2012Metric","","","R52 R69 R80"
"1","51K","Resistor_SMD:R_0805_2012Metric","","","R53"
"1","10K","Resistor_SMD:R_0805_2012Metric","Panasonic ERJ-P06J103V","","R54"
"1","2M2","Resistor_SMD:R_0805_2012Metric","","","R55"
"1","22M","Resistor_SMD:R_0805_2012Metric","Yageo RC0805JR-0722ML","","R57"
"1","4K7","Resistor_SMD:R_0805_2012Metric","Panasonic ERJ-P06J472V","","R58"
"3","22K 1%","Resistor_SMD:R_0805_2012Metric","","","R61 R72 R97"
"2","DNF (2K2 = +10 dB)","Resistor_SMD:R_0805_2012Metric","","DNP","R68 R79"
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
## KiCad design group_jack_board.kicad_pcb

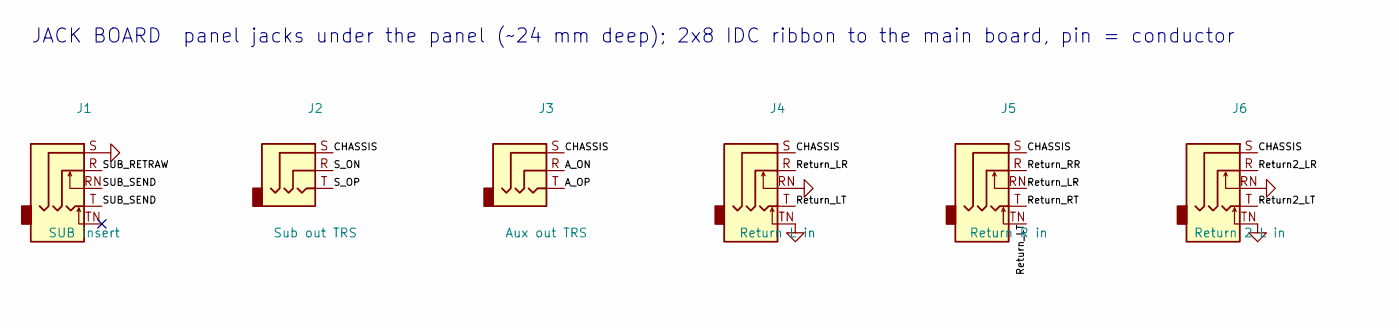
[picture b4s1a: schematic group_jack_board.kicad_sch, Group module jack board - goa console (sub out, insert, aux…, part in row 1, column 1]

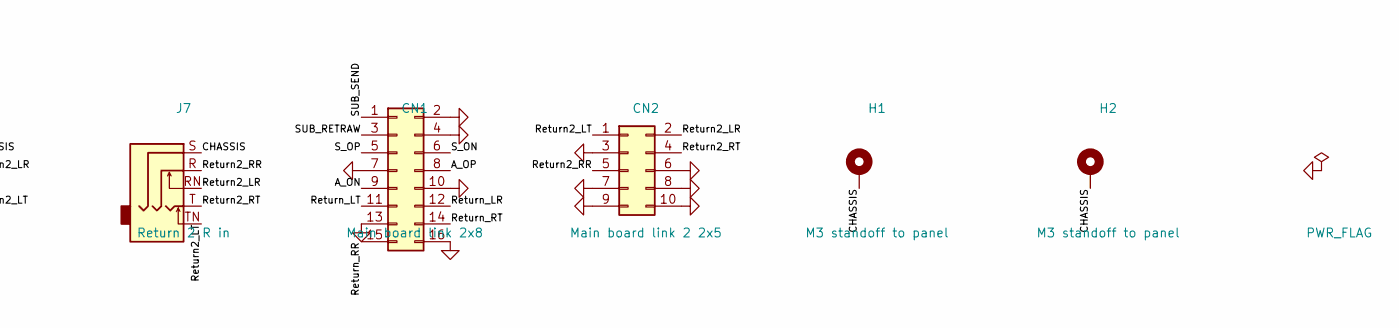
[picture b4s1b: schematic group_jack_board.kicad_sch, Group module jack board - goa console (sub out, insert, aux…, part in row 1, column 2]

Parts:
CN1: Main board link 2x8; IDC-Header_2x08_P2.54mm_Vertical; MPN Wurth 61201621621 (2x8 box header)
CN2: Main board link 2 2x5; IDC-Header_2x05_P2.54mm_Vertical; MPN Wurth 61201021621 (2x5 box header)
H1, H2: M3 standoff to panel; MountingHole_3.2mm_M3_Pad
J1: SUB insert; Jack_6.35mm_Neutrik_NJ6FD-V_Vertical; MPN Neutrik NJ6FD-V
J2: Sub out TRS; Jack_6.35mm_Neutrik_NJ6FD-V_Vertical; MPN Neutrik NJ6FD-V
J3: Aux out TRS; Jack_6.35mm_Neutrik_NJ6FD-V_Vertical; MPN Neutrik NJ6FD-V
J4: Return L in; Jack_6.35mm_Neutrik_NJ6FD-V_Vertical; MPN Neutrik NJ6FD-V
J5: Return R in; Jack_6.35mm_Neutrik_NJ6FD-V_Vertical; MPN Neutrik NJ6FD-V
J6: Return 2 L in; Jack_6.35mm_Neutrik_NJ6FD-V_Vertical; MPN Neutrik NJ6FD-V
J7: Return 2 R in; Jack_6.35mm_Neutrik_NJ6FD-V_Vertical; MPN Neutrik NJ6FD-V

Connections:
/A_ON: CN1.9, J3.R
/A_OP: CN1.8, J3.T
/CHASSIS: H1.1, H2.1, J2.S, J3.S, J4.S, J5.S, J6.S, J7.S
/Return2_LR: CN2.2, J6.R, J7.RN
/Return2_LT: CN2.1, J6.T, J7.TN
/Return2_RR: CN2.5, J7.R
/Return2_RT: CN2.4, J7.T
/Return_LR: CN1.12, J4.R, J5.RN
/Return_LT: CN1.11, J4.T, J5.TN
/Return_RR: CN1.15, J5.R
/Return_RT: CN1.14, J5.T
/SUB_RETRAW: CN1.3, J1.R
/SUB_SEND: CN1.1, J1.RN, J1.T
/S_ON: CN1.6, J2.R
/S_OP: CN1.5, J2.T
GNDA: CN1.2, CN1.4, CN1.7, CN1.10, CN1.13, CN1.16, CN2.3, CN2.6, CN2.7, CN2.8, CN2.9, CN2.10, J1.S, J4.RN, J4.TN, J6.RN, J6.TN

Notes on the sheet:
JACK BOARD panel jacks under the panel (~24 mm deep); 2x8 IDC ribbon to the main board, pin = conductor

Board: 2 copper layers, 11 parts (2 on the bottom side), 16 nets, no tracks yet.

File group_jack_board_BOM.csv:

"Qty","Value","Footprint","MPN","DNP","References"
"1","Main board link 2x8","Connector_IDC:IDC-Header_2x08_P2.54mm_Vertical","Wurth 61201621621 (2x8 box header)","","CN1"
"1","SUB insert","Connector_Audio:Jack_6.35mm_Neutrik_NJ6FD-V_Vertical","Neutrik NJ6FD-V","","J1"
"1","Sub out TRS","Connector_Audio:Jack_6.35mm_Neutrik_NJ6FD-V_Vertical","Neutrik NJ6FD-V","","J2"
"1","Aux out TRS","Connector_Audio:Jack_6.35mm_Neutrik_NJ6FD-V_Vertical","Neutrik NJ6FD-V","","J3"
"1","Return L in","Connector_Audio:Jack_6.35mm_Neutrik_NJ6FD-V_Vertical","Neutrik NJ6FD-V","","J4"
"1","Return R in","Connector_Audio:Jack_6.35mm_Neutrik_NJ6FD-V_Vertical","Neutrik NJ6FD-V","","J5"

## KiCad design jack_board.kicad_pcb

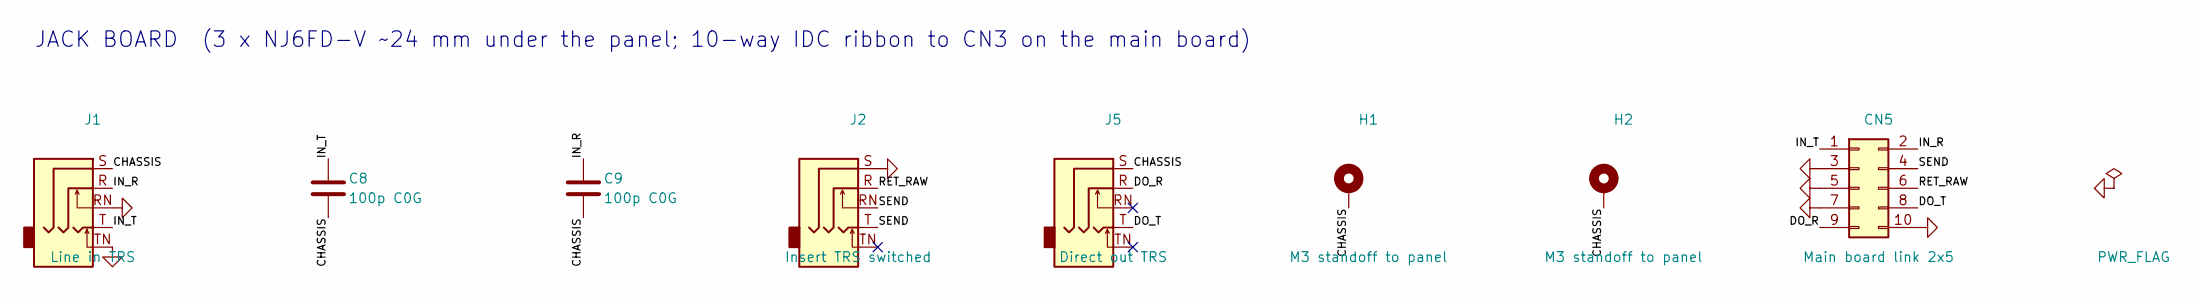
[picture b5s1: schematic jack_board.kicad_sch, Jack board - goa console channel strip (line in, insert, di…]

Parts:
C8, C9: 100p C0G; C_0805_2012Metric; MPN KEMET C0805C101J5GACTU
CN5: Main board link 2x5; IDC-Header_2x05_P2.54mm_Vertical; MPN Wurth 61201021621 (2x5 box header)
H1, H2: M3 standoff to panel; MountingHole_3.2mm_M3_Pad
J1: Line in TRS; Jack_6.35mm_Neutrik_NJ6FD-V_Vertical; MPN Neutrik NJ6FD-V
J2: Insert TRS switched; Jack_6.35mm_Neutrik_NJ6FD-V_Vertical; MPN Neutrik NJ6FD-V
J5: Direct out TRS; Jack_6.35mm_Neutrik_NJ6FD-V_Vertical; MPN Neutrik NJ6FD-V

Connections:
/CHASSIS: C8.2, C9.2, H1.1, H2.1, J1.S, J5.S
/DO_R: CN5.9, J5.R
/DO_T: CN5.8, J5.T
/IN_R: C9.1, CN5.2, J1.R
/IN_T: C8.1, CN5.1, J1.T
/RET_RAW: CN5.6, J2.R
/SEND: CN5.4, J2.RN, J2.T
GNDA: CN5.3, CN5.5, CN5.7, CN5.10, J1.RN, J1.TN, J2.S

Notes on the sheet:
JACK BOARD (3 x NJ6FD-V ~24 mm under the panel; 10-way IDC ribbon to CN3 on the main board)
